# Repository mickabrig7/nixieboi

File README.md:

# ⚡ nixieboi
An open-source Nixie tube clock + PSU using affordable parts from JLCPCB

**Still a WIP as of now**

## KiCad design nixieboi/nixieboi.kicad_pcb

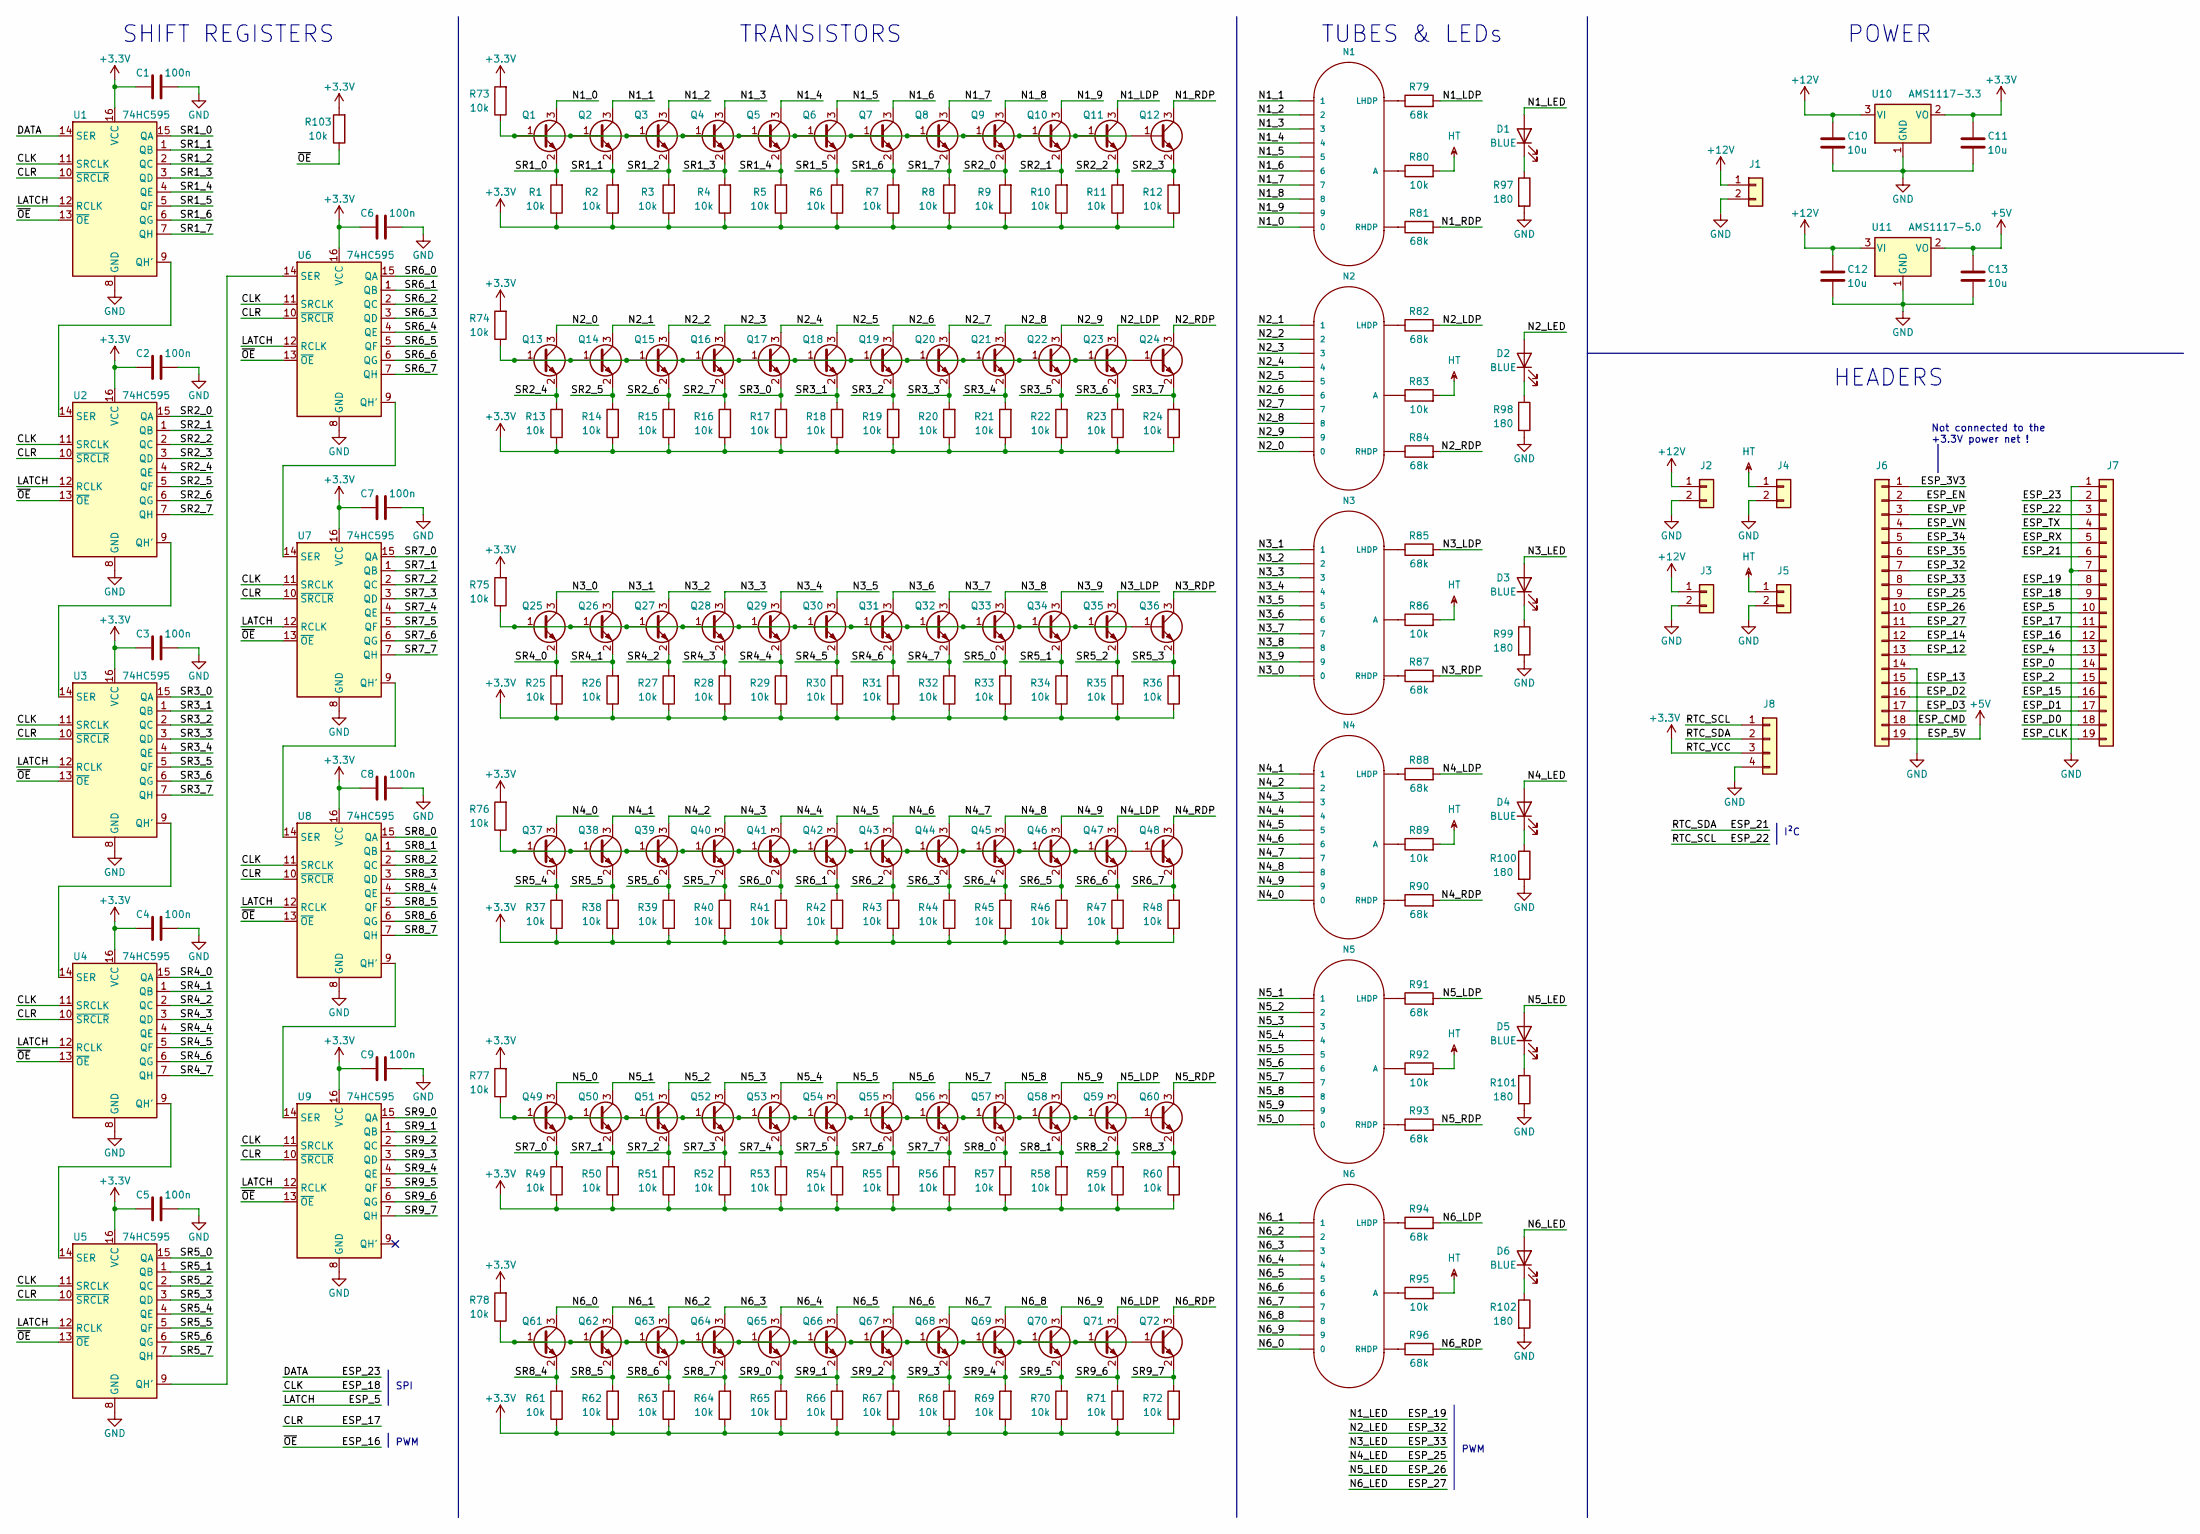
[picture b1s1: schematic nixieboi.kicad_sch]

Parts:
C1, C2, C3, C4, C5, C6, C7, C8, C9: 100n; C_0603_1608Metric; LCSC C14663
C10, C11, C12, C13: 10u; C_0805_2012Metric; LCSC C15850
D1, D2, D3, D4, D5, D6: BLUE; LED_0603_1608Metric; LCSC C72041
J1: Conn_01x02; SolderWire-1sqmm_1x02_P7.8mm_D1.4mm_OD3.9mm
J2, J3, J4, J5: Conn_01x02; PinSocket_1x02_P2.54mm_Vertical
J6, J7: Conn_01x19; PinSocket_1x19_P2.54mm_Vertical
J8: Conn_01x04; PinSocket_1x04_P2.54mm_Vertical
N1, N2, N3, N4, N5, N6: IN-14; nixies-us-IN-14
Q1, Q2, Q3, Q4, Q5, Q6, Q7, Q8, Q9, Q10, Q11, Q12, Q13, Q14, Q15, Q16, Q17, Q18, Q19, Q20, Q21, Q22, Q23, Q24, Q25, Q26, Q27, Q28, Q29, Q30, Q31, Q32, Q33, Q34, Q35, Q36, Q37, Q38, Q39, Q40, Q41, Q42, Q43, Q44, Q45, Q46, Q47, Q48, Q49, Q50, Q51, Q52, Q53, Q54, Q55, Q56, Q57, Q58, Q59, Q60, Q61, Q62, Q63, Q64, Q65, Q66, Q67, Q68, Q69, Q70, Q71, Q72: Q_NPN_BEC; SOT-23; LCSC C8515
R1, R2, R3, R4, R5, R6, R7, R8, R9, R10, R11, R12, R13, R14, R15, R16, R17, R18, R19, R20, R21, R22, R23, R24, R25, R26, R27, R28, R29, R30, R31, R32, R33, R34, R35, R36, R37, R38, R39, R40, R41, R42, R43, R44, R45, R46, R47, R48, R49, R50, R51, R52, R53, R54, R55, R56, R57, R58, R59, R60, R61, R62, R63, R64, R65, R66, R67, R68, R69, R70, R71, R72, R73, R74, R75, R76, R77, R78, R80, R83, R86, R89, R92, R95, R103: 10k; R_0603_1608Metric; LCSC C25804
R79, R81, R82, R84, R85, R87, R88, R90, R91, R93, R94, R96: 68k; R_0603_1608Metric; LCSC C23231
R97, R98, R99, R100, R101, R102: 180; R_0603_1608Metric; LCSC C22828
U1, U2, U3, U4, U5, U6, U7, U8, U9: 74HC595; SOIC-16_3.9x9.9mm_P1.27mm; LCSC C5947
U10: AMS1117-3.3; SOT-223-3_TabPin2; LCSC C6186
U11: AMS1117-5.0; SOT-223-3_TabPin2; LCSC C6187

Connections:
+3V3: C1.1, C2.1, C3.1, C4.1, C5.1, C6.1, C7.1, C8.1, C9.1, C11.1, J8.3, R1.1, R2.1, R3.1, R4.1, R5.1, R6.1, R7.1, R8.1, R9.1, R10.1, R11.1, R12.1, R13.1, R14.1, R15.1, R16.1, R17.1, R18.1, R19.1, R20.1, R21.1, R22.1, R23.1, R24.1, R25.1, R26.1, R27.1, R28.1, R29.1, R30.1, R31.1, R32.1, R33.1, R34.1, R35.1, R36.1, R37.1, R38.1, R39.1, R40.1, R41.1, R42.1, R43.1, R44.1, R45.1, R46.1, R47.1, R48.1, R49.1, R50.1, R51.1, R52.1, R53.1, R54.1, R55.1, R56.1, R57.1, R58.1, R59.1, R60.1, R61.1, R62.1, R63.1, R64.1, R65.1, R66.1, R67.1, R68.1, R69.1, R70.1, R71.1, R72.1, R73.2, R74.2, R75.2, R76.2, R77.2, R78.2, R103.2, U1.16 (VCC), U2.16 (VCC), U3.16 (VCC), U4.16 (VCC), U5.16 (VCC), U6.16 (VCC), U7.16 (VCC), U8.16 (VCC), U9.16 (VCC), U10.2 (VO)
+5V: C13.1, J6.19, U11.2 (VO)
+12V: C10.1, C12.1, J1.1, J2.1, J3.1, U10.3 (VI), U11.3 (VI)
/CLK: J7.9, U1.11 (SRCLK), U2.11 (SRCLK), U3.11 (SRCLK), U4.11 (SRCLK), U5.11 (SRCLK), U6.11 (SRCLK), U7.11 (SRCLK), U8.11 (SRCLK), U9.11 (SRCLK)
/CLR: J7.11, U1.10 (~SRCLR), U2.10 (~SRCLR), U3.10 (~SRCLR), U4.10 (~SRCLR), U5.10 (~SRCLR), U6.10 (~SRCLR), U7.10 (~SRCLR), U8.10 (~SRCLR), U9.10 (~SRCLR)
/DATA: J7.2, U1.14 (SER)
/ESP_0: J7.14
/ESP_2: J7.15
/ESP_3V3: J6.1
/ESP_4: J7.13
/ESP_5: J7.10, U1.12 (RCLK), U2.12 (RCLK), U3.12 (RCLK), U4.12 (RCLK), U5.12 (RCLK), U6.12 (RCLK), U7.12 (RCLK), U8.12 (RCLK), U9.12 (RCLK)
/ESP_12: J6.13
/ESP_13: J6.15
/ESP_14: J6.12
/ESP_15: J7.16
/ESP_16: J7.12, R103.1, U1.13 (~OE), U2.13 (~OE), U3.13 (~OE), U4.13 (~OE), U5.13 (~OE), U6.13 (~OE), U7.13 (~OE), U8.13 (~OE), U9.13 (~OE)
/ESP_19: D1.2 (A), J7.8
/ESP_21: J7.6, J8.2
/ESP_22: J7.3, J8.1
/ESP_25: D4.2 (A), J6.9
/ESP_26: D5.2 (A), J6.10
/ESP_32: D2.2 (A), J6.7
/ESP_33: D3.2 (A), J6.8
/ESP_34: J6.5
/ESP_35: J6.6
/ESP_CLK: J7.19
/ESP_CMD: J6.18
/ESP_D0: J7.18
/ESP_D1: J7.17
/ESP_D2: J6.16
/ESP_D3: J6.17
/ESP_EN: J6.2
/ESP_RX: J7.5
/ESP_TX: J7.4
/ESP_VN: J6.4
/ESP_VP: J6.3
/N1_0: N1.0, Q1.3 (C)
/N1_1: N1.1, Q2.3 (C)
/N1_2: N1.2, Q3.3 (C)
/N1_3: N1.3, Q4.3 (C)
/N1_4: N1.4, Q5.3 (C)
/N1_5: N1.5, Q6.3 (C)
/N1_6: N1.6, Q7.3 (C)
/N1_7: N1.7, Q8.3 (C)
/N1_8: N1.8, Q9.3 (C)
/N1_9: N1.9, Q10.3 (C)
/N1_LDP: Q11.3 (C), R79.2
/N1_RDP: Q12.3 (C), R81.2
/N2_0: N2.0, Q13.3 (C)
/N2_1: N2.1, Q14.3 (C)
/N2_2: N2.2, Q15.3 (C)
/N2_3: N2.3, Q16.3 (C)
/N2_4: N2.4, Q17.3 (C)
/N2_5: N2.5, Q18.3 (C)
/N2_6: N2.6, Q19.3 (C)
/N2_7: N2.7, Q20.3 (C)
/N2_8: N2.8, Q21.3 (C)
/N2_9: N2.9, Q22.3 (C)
/N2_LDP: Q23.3 (C), R82.2
/N2_RDP: Q24.3 (C), R84.2
/N3_0: N3.0, Q25.3 (C)
/N3_1: N3.1, Q26.3 (C)
/N3_2: N3.2, Q27.3 (C)
/N3_3: N3.3, Q28.3 (C)
/N3_4: N3.4, Q29.3 (C)
/N3_5: N3.5, Q30.3 (C)
/N3_6: N3.6, Q31.3 (C)
/N3_7: N3.7, Q32.3 (C)
/N3_8: N3.8, Q33.3 (C)
/N3_9: N3.9, Q34.3 (C)
/N3_LDP: Q35.3 (C), R85.2
/N3_RDP: Q36.3 (C), R87.2
/N4_0: N4.0, Q37.3 (C)
/N4_1: N4.1, Q38.3 (C)
/N4_2: N4.2, Q39.3 (C)
/N4_3: N4.3, Q40.3 (C)
/N4_4: N4.4, Q41.3 (C)
/N4_5: N4.5, Q42.3 (C)
/N4_6: N4.6, Q43.3 (C)
/N4_7: N4.7, Q44.3 (C)
/N4_8: N4.8, Q45.3 (C)
/N4_9: N4.9, Q46.3 (C)
/N4_LDP: Q47.3 (C), R88.2
/N4_RDP: Q48.3 (C), R90.2
/N5_0: N5.0, Q49.3 (C)
/N5_1: N5.1, Q50.3 (C)
/N5_2: N5.2, Q51.3 (C)
/N5_3: N5.3, Q52.3 (C)
/N5_4: N5.4, Q53.3 (C)
/N5_5: N5.5, Q54.3 (C)
/N5_6: N5.6, Q55.3 (C)
/N5_7: N5.7, Q56.3 (C)
/N5_8: N5.8, Q57.3 (C)
/N5_9: N5.9, Q58.3 (C)
/N5_LDP: Q59.3 (C), R91.2
/N5_RDP: Q60.3 (C), R93.2
/N6_0: N6.0, Q61.3 (C)
/N6_1: N6.1, Q62.3 (C)
/N6_2: N6.2, Q63.3 (C)
/N6_3: N6.3, Q64.3 (C)
/N6_4: N6.4, Q65.3 (C)
/N6_5: N6.5, Q66.3 (C)
/N6_6: N6.6, Q67.3 (C)
/N6_7: N6.7, Q68.3 (C)
/N6_8: N6.8, Q69.3 (C)
/N6_9: N6.9, Q70.3 (C)
/N6_LDP: Q71.3 (C), R94.2
/N6_LED: D6.2 (A), J6.11
/N6_RDP: Q72.3 (C), R96.2
/SR1_0: Q1.2 (E), R1.2, U1.15 (QA)
/SR1_1: Q2.2 (E), R2.2, U1.1 (QB)
/SR1_2: Q3.2 (E), R3.2, U1.2 (QC)
/SR1_3: Q4.2 (E), R4.2, U1.3 (QD)
/SR1_4: Q5.2 (E), R5.2, U1.4 (QE)
/SR1_5: Q6.2 (E), R6.2, U1.5 (QF)
/SR1_6: Q7.2 (E), R7.2, U1.6 (QG)
/SR1_7: Q8.2 (E), R8.2, U1.7 (QH)
/SR2_0: Q9.2 (E), R9.2, U2.15 (QA)
/SR2_1: Q10.2 (E), R10.2, U2.1 (QB)
/SR2_2: Q11.2 (E), R11.2, U2.2 (QC)
/SR2_3: Q12.2 (E), R12.2, U2.3 (QD)
/SR2_4: Q13.2 (E), R13.2, U2.4 (QE)
/SR2_5: Q14.2 (E), R14.2, U2.5 (QF)
/SR2_6: Q15.2 (E), R15.2, U2.6 (QG)
/SR2_7: Q16.2 (E), R16.2, U2.7 (QH)
/SR3_0: Q17.2 (E), R17.2, U3.15 (QA)
/SR3_1: Q18.2 (E), R18.2, U3.1 (QB)
/SR3_2: Q19.2 (E), R19.2, U3.2 (QC)
/SR3_3: Q20.2 (E), R20.2, U3.3 (QD)
/SR3_4: Q21.2 (E), R21.2, U3.4 (QE)
/SR3_5: Q22.2 (E), R22.2, U3.5 (QF)
/SR3_6: Q23.2 (E), R23.2, U3.6 (QG)
/SR3_7: Q24.2 (E), R24.2, U3.7 (QH)
/SR4_0: Q25.2 (E), R25.2, U4.15 (QA)
/SR4_1: Q26.2 (E), R26.2, U4.1 (QB)
/SR4_2: Q27.2 (E), R27.2, U4.2 (QC)
/SR4_3: Q28.2 (E), R28.2, U4.3 (QD)
/SR4_4: Q29.2 (E), R29.2, U4.4 (QE)
/SR4_5: Q30.2 (E), R30.2, U4.5 (QF)
/SR4_6: Q31.2 (E), R31.2, U4.6 (QG)
/SR4_7: Q32.2 (E), R32.2, U4.7 (QH)
/SR5_0: Q33.2 (E), R33.2, U5.15 (QA)
/SR5_1: Q34.2 (E), R34.2, U5.1 (QB)
/SR5_2: Q35.2 (E), R35.2, U5.2 (QC)
/SR5_3: Q36.2 (E), R36.2, U5.3 (QD)
/SR5_4: Q37.2 (E), R37.2, U5.4 (QE)
/SR5_5: Q38.2 (E), R38.2, U5.5 (QF)
/SR5_6: Q39.2 (E), R39.2, U5.6 (QG)
/SR5_7: Q40.2 (E), R40.2, U5.7 (QH)
/SR6_0: Q41.2 (E), R41.2, U6.15 (QA)
/SR6_1: Q42.2 (E), R42.2, U6.1 (QB)
/SR6_2: Q43.2 (E), R43.2, U6.2 (QC)
/SR6_3: Q44.2 (E), R44.2, U6.3 (QD)
/SR6_4: Q45.2 (E), R45.2, U6.4 (QE)
/SR6_5: Q46.2 (E), R46.2, U6.5 (QF)
/SR6_6: Q47.2 (E), R47.2, U6.6 (QG)
/SR6_7: Q48.2 (E), R48.2, U6.7 (QH)
/SR7_0: Q49.2 (E), R49.2, U7.15 (QA)
/SR7_1: Q50.2 (E), R50.2, U7.1 (QB)
/SR7_2: Q51.2 (E), R51.2, U7.2 (QC)
/SR7_3: Q52.2 (E), R52.2, U7.3 (QD)
/SR7_4: Q53.2 (E), R53.2, U7.4 (QE)
/SR7_5: Q54.2 (E), R54.2, U7.5 (QF)
/SR7_6: Q55.2 (E), R55.2, U7.6 (QG)
/SR7_7: Q56.2 (E), R56.2, U7.7 (QH)
/SR8_0: Q57.2 (E), R57.2, U8.15 (QA)
/SR8_1: Q58.2 (E), R58.2, U8.1 (QB)
/SR8_2: Q59.2 (E), R59.2, U8.2 (QC)
/SR8_3: Q60.2 (E), R60.2, U8.3 (QD)
/SR8_4: Q61.2 (E), R61.2, U8.4 (QE)
/SR8_5: Q62.2 (E), R62.2, U8.5 (QF)
/SR8_6: Q63.2 (E), R63.2, U8.6 (QG)
/SR8_7: Q64.2 (E), R64.2, U8.7 (QH)
/SR9_0: Q65.2 (E), R65.2, U9.15 (QA)
/SR9_1: Q66.2 (E), R66.2, U9.1 (QB)
/SR9_2: Q67.2 (E), R67.2, U9.2 (QC)
/SR9_3: Q68.2 (E), R68.2, U9.3 (QD)
/SR9_4: Q69.2 (E), R69.2, U9.4 (QE)
/SR9_5: Q70.2 (E), R70.2, U9.5 (QF)
/SR9_6: Q71.2 (E), R71.2, U9.6 (QG)
/SR9_7: Q72.2 (E), R72.2, U9.7 (QH)
GND: C1.2, C2.2, C3.2, C4.2, C5.2, C6.2, C7.2, C8.2, C9.2, C10.2, C11.2, C12.2, C13.2, J1.2, J2.2, J3.2, J4.2, J5.2, J6.14, J7.1, J7.7, J8.4, R97.2, R98.2, R99.2, R100.2, R101.2, R102.2, U1.8 (GND), U2.8 (GND), U3.8 (GND), U4.8 (GND), U5.8 (GND), U6.8 (GND), U7.8 (GND), U8.8 (GND), U9.8 (GND), U10.1 (GND), U11.1 (GND)
HT: J4.1, J5.1, R80.2, R83.2, R86.2, R89.2, R92.2, R95.2
unnamed: D1.1 (K), R97.1
unnamed: D2.1 (K), R98.1
unnamed: D3.1 (K), R99.1
unnamed: D4.1 (K), R100.1
unnamed: D5.1 (K), R101.1
unnamed: D6.1 (K), R102.1
unnamed: N1.A, R80.1
unnamed: N1.LHDP, R79.1
unnamed: N1.RHDP, R81.1
unnamed: N2.A, R83.1
unnamed: N2.LHDP, R82.1
unnamed: N2.RHDP, R84.1
unnamed: N3.A, R86.1
unnamed: N3.LHDP, R85.1
unnamed: N3.RHDP, R87.1
unnamed: N4.A, R89.1
unnamed: N4.LHDP, R88.1
unnamed: N4.RHDP, R90.1
unnamed: N5.A, R92.1
unnamed: N5.LHDP, R91.1
unnamed: N5.RHDP, R93.1
unnamed: N6.A, R95.1
unnamed: N6.LHDP, R94.1
unnamed: N6.RHDP, R96.1
unnamed: Q1.1 (B), Q2.1 (B), Q3.1 (B), Q4.1 (B), Q5.1 (B), Q6.1 (B), Q7.1 (B), Q8.1 (B), Q9.1 (B), Q10.1 (B), Q11.1 (B), Q12.1 (B), R73.1
unnamed: Q13.1 (B), Q14.1 (B), Q15.1 (B), Q16.1 (B), Q17.1 (B), Q18.1 (B), Q19.1 (B), Q20.1 (B), Q21.1 (B), Q22.1 (B), Q23.1 (B), Q24.1 (B), R74.1
unnamed: Q25.1 (B), Q26.1 (B), Q27.1 (B), Q28.1 (B), Q29.1 (B), Q30.1 (B), Q31.1 (B), Q32.1 (B), Q33.1 (B), Q34.1 (B), Q35.1 (B), Q36.1 (B), R75.1
unnamed: Q37.1 (B), Q38.1 (B), Q39.1 (B), Q40.1 (B), Q41.1 (B), Q42.1 (B), Q43.1 (B), Q44.1 (B), Q45.1 (B), Q46.1 (B), Q47.1 (B), Q48.1 (B), R76.1
unnamed: Q49.1 (B), Q50.1 (B), Q51.1 (B), Q52.1 (B), Q53.1 (B), Q54.1 (B), Q55.1 (B), Q56.1 (B), Q57.1 (B), Q58.1 (B), Q59.1 (B), Q60.1 (B), R77.1
unnamed: Q61.1 (B), Q62.1 (B), Q63.1 (B), Q64.1 (B), Q65.1 (B), Q66.1 (B), Q67.1 (B), Q68.1 (B), Q69.1 (B), Q70.1 (B), Q71.1 (B), Q72.1 (B), R78.1
unnamed: U1.9 (QH'), U2.14 (SER)
unnamed: U2.9 (QH'), U3.14 (SER)
unnamed: U3.9 (QH'), U4.14 (SER)
unnamed: U4.9 (QH'), U5.14 (SER)
unnamed: U5.9 (QH'), U6.14 (SER)
unnamed: U6.9 (QH'), U7.14 (SER)
unnamed: U7.9 (QH'), U8.14 (SER)
unnamed: U8.9 (QH'), U9.14 (SER)

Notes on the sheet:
POWER
PWM
Not connected to the +3.3V power net !
SPI
TRANSISTORS
SHIFT REGISTERS
HEADERS
TUBES & LEDs
I²C

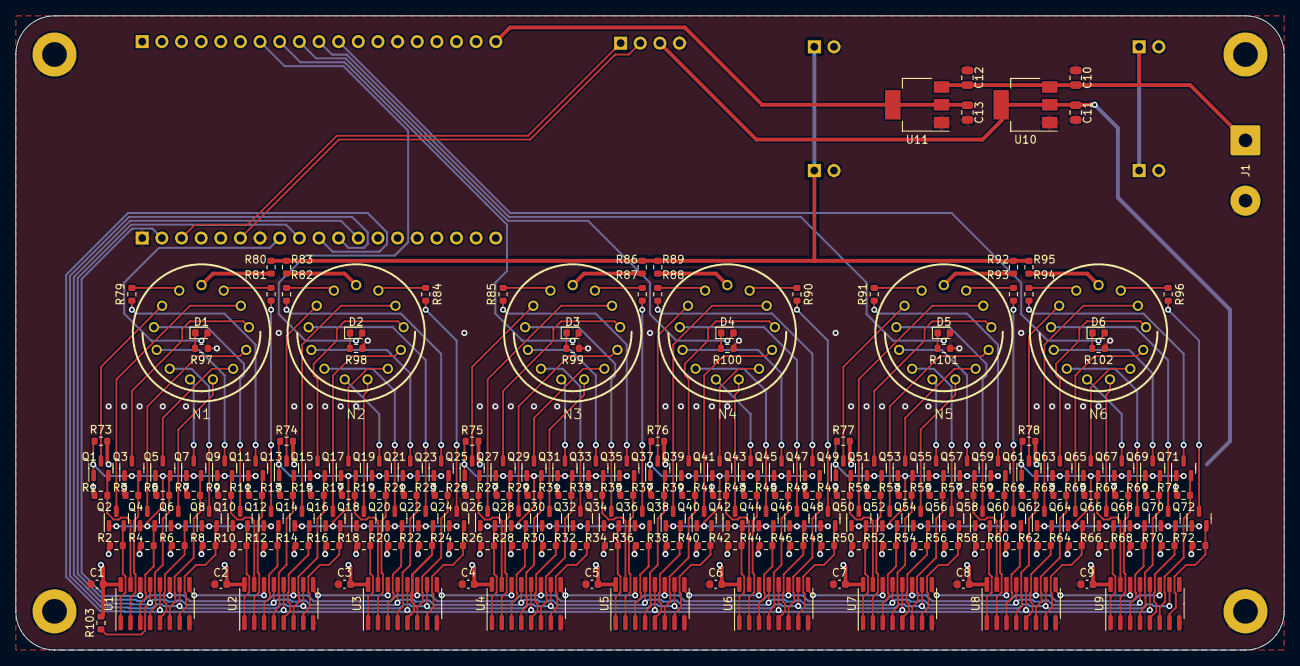
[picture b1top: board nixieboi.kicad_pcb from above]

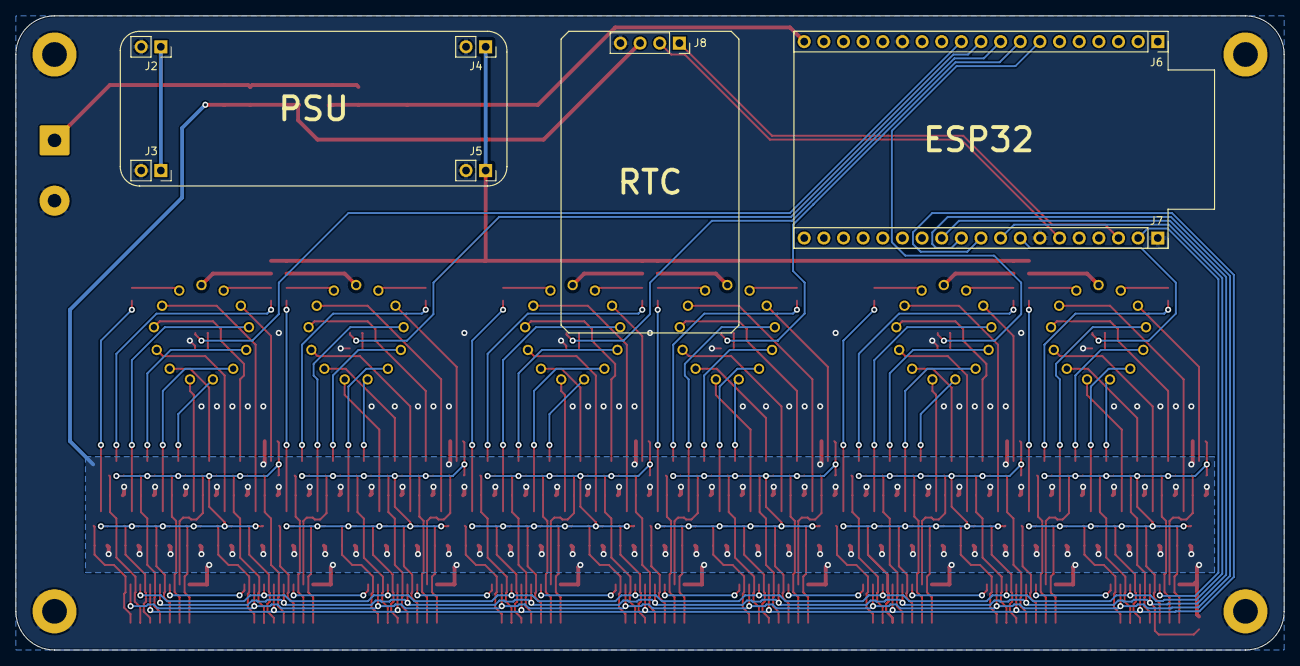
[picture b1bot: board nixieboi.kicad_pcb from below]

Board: 2 copper layers, 164.0 x 82.0 mm, 219 parts (7 on the bottom side), 200 nets.

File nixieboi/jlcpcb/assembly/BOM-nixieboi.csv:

Comment,Designator,Footprint,LCSC
100n,"C1,C2,C3,C4,C5,C6,C7,C8,C9",C_0603_1608Metric,C14663
10u,"C10,C11,C12,C13",C_0805_2012Metric,C15850
180,"R100,R101,R102,R97,R98,R99",R_0603_1608Metric,C22828
68k,"R79,R81,R82,R84,R85,R87,R88,R90,R91,R93,R94,R96",R_0603_1608Metric,C23231
10k,"R1,R10,R103,R11,R12,R13,R14,R15,R16,R17,R18,R19,R2,R20,R21,R22,R23,R24,R25,R26,R27,R28,R29,R3,R30,R31,R32,R33,R34,R35,R36,R37,R38,R39,R4,R40,R41,R42,R43,R44,R45,R46,R47,R48,R49,R5,R50,R51,R52,R53,R54,R55,R56,R57,R58,R59,R6,R60,R61,R62,R63,R64,R65,R66,R67,R68,R69,R7,R70,R71,R72,R73,R74,R75,R76,R77,R78,R8,R80,R83,R86,R89,R9,R92,R95",R_0603_1608Metric,C25804
74HC595,"U1,U2,U3,U4,U5,U6,U7,U8,U9",SOIC-16_3.9x9.9mm_P1.27mm,C5947
AMS1117-3.3,U10,SOT-223-3_TabPin2,C6186
AMS1117-5.0,U11,SOT-223-3_TabPin2,C6187
BLUE,"D1,D2,D3,D4,D5,D6",LED_0603_1608Metric,C72041
Q_NPN_BEC,"Q1,Q10,Q11,Q12,Q13,Q14,Q15,Q16,Q17,Q18,Q19,Q2,Q20,Q21,Q22,Q23,Q24,Q25,Q26,Q27,Q28,Q29,Q3,Q30,Q31,Q32,Q33,Q34,Q35,Q36,Q37,Q38,Q39,Q4,Q40,Q41,Q42,Q43,Q44,Q45,Q46,Q47,Q48,Q49,Q5,Q50,Q51,Q52,Q53,Q54,Q55,Q56,Q57,Q58,Q59,Q6,Q60,Q61,Q62,Q63,Q64,Q65,Q66,Q67,Q68,Q69,Q7,Q70,Q71,Q72,Q8,Q9",SOT-23,C8515

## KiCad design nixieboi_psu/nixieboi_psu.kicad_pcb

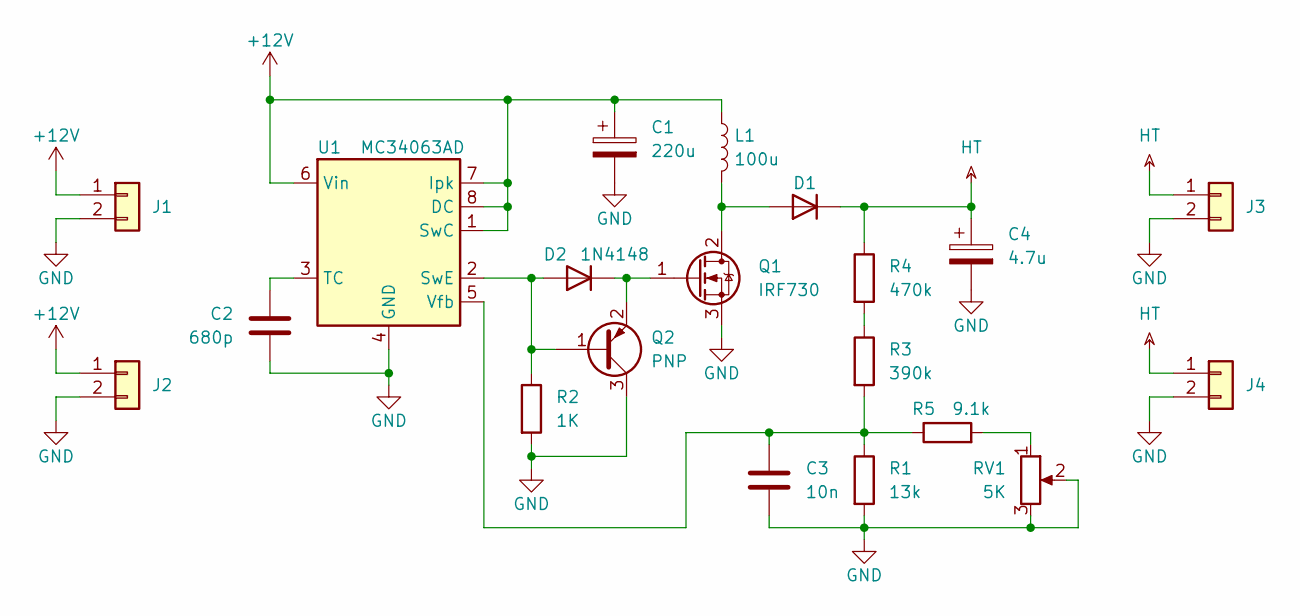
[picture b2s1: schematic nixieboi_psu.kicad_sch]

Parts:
C1: 220u; CP_Radial_D8.0mm_P3.50mm
C2: 680p; C_0603_1608Metric; LCSC C1630
C3: 10n; C_0603_1608Metric; LCSC C57112
C4: 4.7u; CP_Radial_D8.0mm_P3.50mm
D1: D; D_SMA; LCSC C412437
D2: 1N4148; D_SOD-123; LCSC C81598
J1, J2, J3, J4: Conn_01x02; PinHeader_1x02_P2.54mm_Vertical
L1: 100u; L_Radial_D9.5mm_P5.00mm_Fastron_07HVP
Q1: IRF730; TO-220-3_Vertical
Q2: PNP; SOT-23; LCSC C2149
R1: 13k; R_0603_1608Metric; LCSC C22797
R2: 1K; R_0603_1608Metric; LCSC C21190
R3: 390k; R_0603_1608Metric; LCSC C23150
R4: 470k; R_0603_1608Metric; LCSC C23178
R5: 9.1k; R_0603_1608Metric; LCSC C23260
RV1: 5K; Potentiometer_Trimmer-EVM3E
U1: MC34063AD; SOIC-8_3.9x4.9mm_P1.27mm; LCSC C32078

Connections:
+12V: C1.1, J1.1, J2.1, L1.1, U1.1 (SwC), U1.6 (Vin), U1.7 (Ipk), U1.8 (DC)
GND: C1.2, C2.2, C3.1, C4.2, J1.2, J2.2, J3.2, J4.2, Q1.3 (S), Q2.3 (C), R1.2, R2.2, RV1.2, RV1.3, U1.4 (GND)
HT: C4.1, D1.1 (K), J3.1, J4.1, R4.1
unnamed: C2.1, U1.3 (TC)
unnamed: C3.2, R1.1, R3.2, R5.1, U1.5 (Vfb)
unnamed: D1.2 (A), L1.2, Q1.2 (D)
unnamed: D2.1 (K), Q1.1 (G), Q2.2 (E)
unnamed: D2.2 (A), Q2.1 (B), R2.1, U1.2 (SwE)
unnamed: R3.1, R4.2
unnamed: R5.2, RV1.1

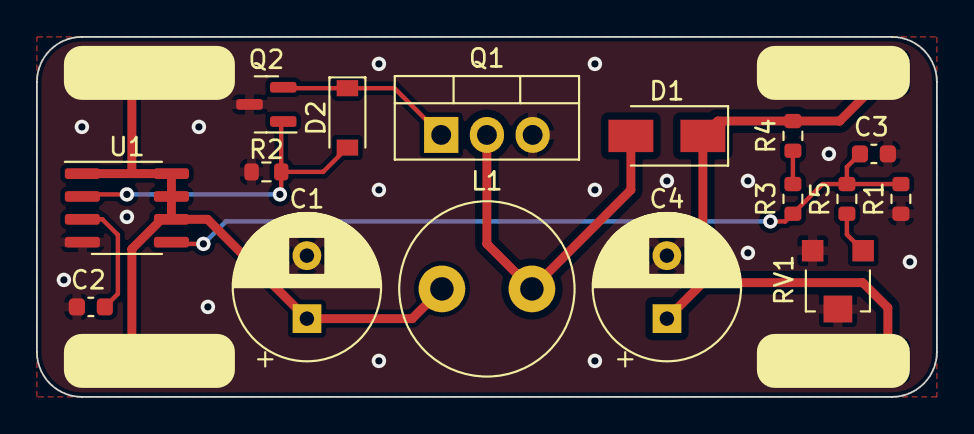
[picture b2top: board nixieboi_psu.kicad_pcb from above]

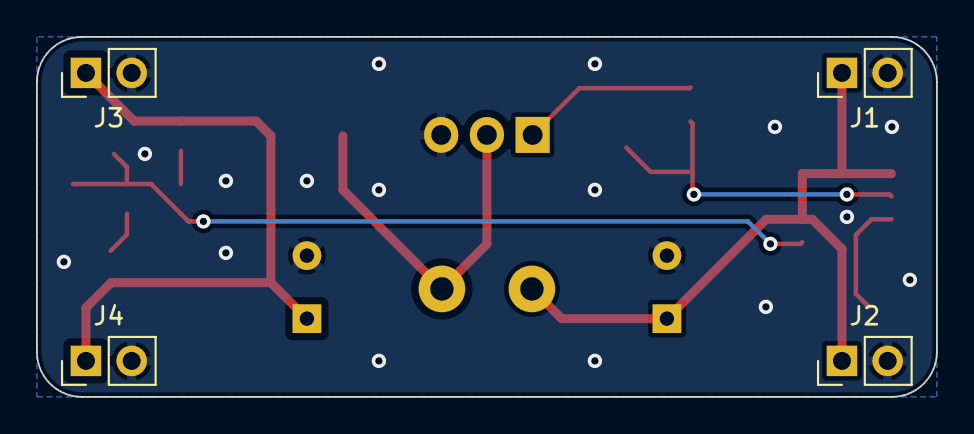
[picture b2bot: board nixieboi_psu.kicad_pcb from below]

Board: 2 copper layers, 50.0 x 20.0 mm, 20 parts (4 on the bottom side), 10 nets.

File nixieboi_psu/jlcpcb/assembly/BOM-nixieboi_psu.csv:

Comment,Designator,Footprint,LCSC
680p,C2,C_0603_1608Metric,C1630
1K,R2,R_0603_1608Metric,C21190
PNP,Q2,SOT-23,C2149
13k,R1,R_0603_1608Metric,C22797
390k,R3,R_0603_1608Metric,C23150
470k,R4,R_0603_1608Metric,C23178
9.1k,R5,R_0603_1608Metric,C23260
MC34063AD,U1,SOIC-8_3.9x4.9mm_P1.27mm,C32078
D,D1,D_SMA,C412437
10n,C3,C_0603_1608Metric,C57112
1N4148,D2,D_SOD-123,C81598

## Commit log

2022-11-08 Initial commit (WIP)
